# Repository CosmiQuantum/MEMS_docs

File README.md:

# MEMS_docs
Hello and welcome to MEMS in LOUD.  This repository is intended to serve as a central (and sharable) location with instructions and datasheets for the MEMS system.  Control code for the system is stored in the [MEMS_Ctrl](https://github.com/CosmiQuantum/MEMS_Ctrl) repo.  It is kept separate so that users of the system do not need to download this entire handbook to run things.  

This documentation is broken into four categories: 
1. ``LOUD_Electrical`` contains information about the DC cable chain.
2. ``LOUD_Optical`` contains information about the laser routing and control. 
3. ``LOUD_Hardware`` contains information about the design and assembly of the MEMS and qubit housings
4. ``MEMS_Mirrors`` contains mirror datasheets as well as instructions for running the MEMS Windows software (which serves as an alternative to the usb/serial control software linked above).  

----
## What is MEMS
The MEMS laser system can be used to sweep a laser beam across the surface of a given quantum device.  In LOUD, the system is currently hooked up to a 6-qubit [silicon transmon chip](https://github.com/CosmiQuantum/MEMS_docs/blob/main/LOUD_hardware/silicon_qubit_setup.md) from Robert Mcdermott's group at the University of Wisconsin.  A block diagram of the system is shown here:

*Image credit: Kelly Stifter*

-----
## Helpful Links
**MEMS google drive:** https://drive.google.com/drive/folders/1IxKxNAd-OEq4rYUD9z-39MRGrSPkV5Ok?usp=drive_link

**MEMS QSC confluence:** https://confluence.qscience.org/display/1HTCSA/MEMS+System

**Running slide decks:**
* [Planning hardware/wiring for LOUD (8/2022 - present)](https://docs.google.com/presentation/d/1KGMi7ChWB6aNYRg5WBvVhE06Tzbi3BEKmCEu2dWy-tE/edit#slide=id.g2295b13efb6_0_0)
* [MEMS + qubits tests in LOUD (5/2023 - present](https://docs.google.com/presentation/d/11gDJgIZLsgrVuI4iNvbL_12GYMmGFXiDUxQpM1qBsPI/edit#slide=id.g256b424b535_0_0)

----  
## Onboarding resources:
* [Kelly's description of the MEMS program, pre-installation in LOUD (8/2022)](https://docs.google.com/presentation/d/1EdDBv1uNEWqCI73cme1L7-Cg87s-V7iwivkqoPncXTw/edit#slide=id.p)
* [Folder with presentation slides](https://drive.google.com/drive/folders/1UWY2XsLM5ypoSD7gy8bRqhrUESGADwUB)
* Talks available on youtube:
  * *Note that these are both horribly out of date, and do not include results of cold testing. Nevertheless, they may be helpful for students trying to familiarize themselves with the MEMS system & its big-picture goals*
  * [Kelly Stifter, Snowmass 2022](https://www.youtube.com/watch?v=Wy0oarMECdM) (awarded best poster!)
  * [Kelly Stifter, QSC summer school 2022](https://youtu.be/VW6oRTCWZw8?t=2815)

----
## Contact
Please reach out if you have questions or comments.  Even if I'm not around, I'm more than happy to help clarify or troubleshoot.  My contact info is listed here:

| Name | Email | Phone? |
| --- | --- | --- |
| Hannah Magoon | hwmagoon@stanford.edu | 508-665-8282 | 

*I don't want to volunteer the contact info of others, but if you are reading this and have a baseline understanding of the system, please add your name to the table & edit this documentation as you see fit.*

----
## Archived MEMS Links

**MEMS at FNAL photo album:** 
* https://photos.google.com/share/AF1QipMmqoWbn3RVLo4tqv78I0vS4r6iMvlEblVydgLS6NxNUOYILnwoK53Qj7WT-ZwPpg?key=R2o0NlpHQnVBcFBGemhvR2Q4Rk5NVkxOU0pIbUpB
* contains pictures from Lab A and first installation in LOUD (i.e. all MEMS photos from the year 2022)

**MEMS on the NEXUS confluence:** 
* https://confluence.slac.stanford.edu/display/NEXUS/MEMS+mirror+project
* Contains information about the Lab A setup, and project notes pre-Kelly/Hannah
* (Note that more recent documentation can be found on the [QSC confluence](https://confluence.qscience.org/display/1HTCSA/MEMS+System))
  
**Running Slide Decks**
* [MEMS Project Status (1/2023 - present)](https://docs.google.com/presentation/d/1zzwaTrPCd6iAJnR8lv24U-RBMRbJIyfRHySXNWpxKuQ/edit)
* [First cold test in Lab A with Adam's KID (3/2022 - 9/2022)](https://docs.google.com/presentation/d/1kEx_I9y4r-qSOtKWM2qjZcWUeaD-5IixSUfKqjTUWgM/edit#slide=id.g15028d90891_0_0)
* [Lab A datataking (9/2022 - 12/2022)](https://docs.google.com/presentation/d/1aT7D16LCWrzIWNsnplRhRge39xQKbSNosBU8oI7OwhY/edit#slide=id.g1c52c33cf82_0_0)
* [Initial CAD design (3/2022)](https://docs.google.com/presentation/d/1Ot2j-huilQjQEyUlkndx-m_U-fPALiF_-bEYakDAZJo/edit#slide=id.g11e369db084_0_0)
* [Reflective focusing at SLAC (11/2022)](https://docs.google.com/presentation/d/1IvIgyGEyYdLRP5Z9ZWvfET_vtNke7xzl7hGHc7-LfRQ/edit#slide=id.p)
----

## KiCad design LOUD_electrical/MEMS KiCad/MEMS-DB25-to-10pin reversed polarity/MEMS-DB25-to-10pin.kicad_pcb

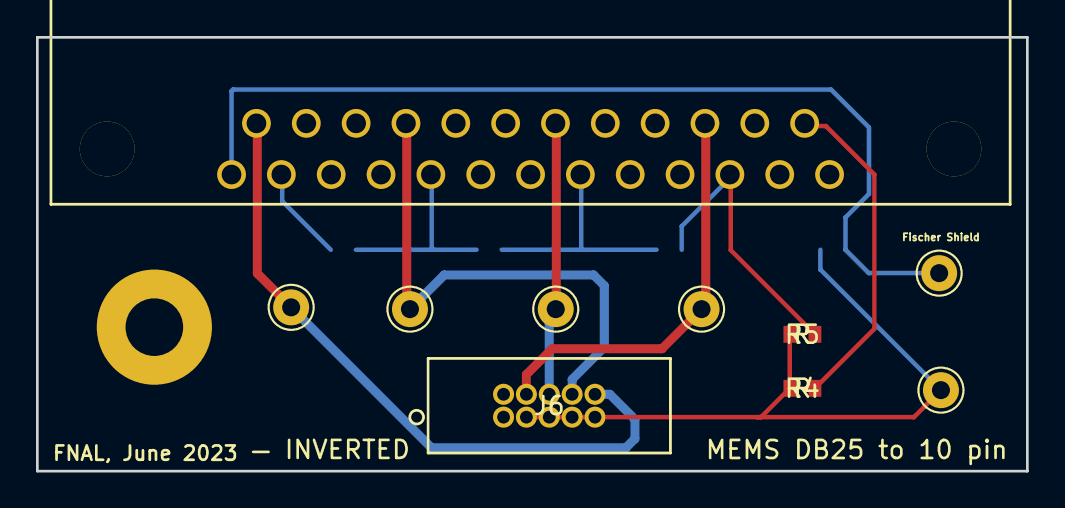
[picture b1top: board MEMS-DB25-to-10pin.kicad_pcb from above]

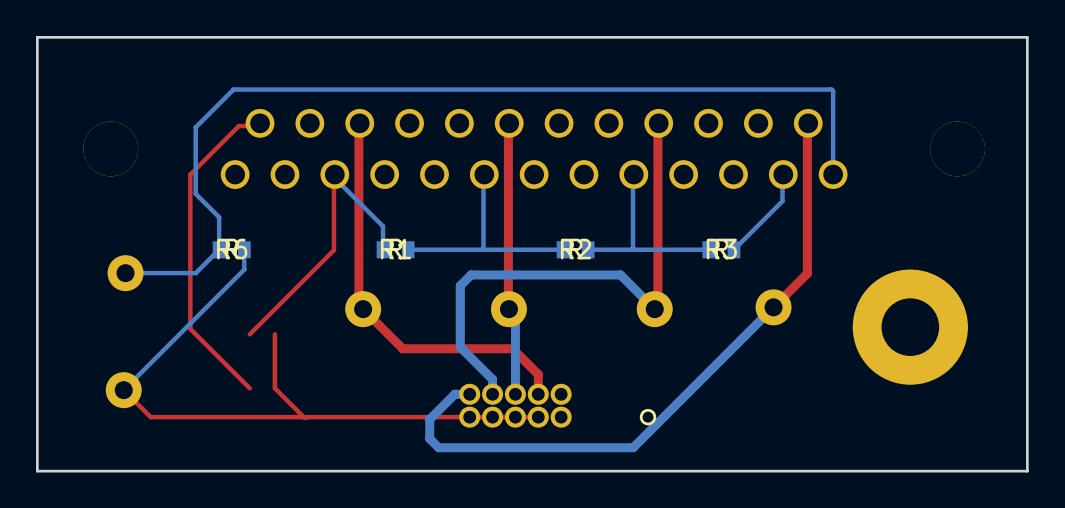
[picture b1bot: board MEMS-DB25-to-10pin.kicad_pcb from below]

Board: 2 copper layers, 55.0 x 24.1 mm, 15 parts (4 on the bottom side), 11 nets.

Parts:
H1: MountingHole; MountingHole_3.2mm_M3_Pad
J1: DB25_Female_MountingHoles; digikey_DSub_NOR1137-ND
J2: X+; Pin_D1.0mm_L10.0mm
J3: X-; Pin_D1.0mm_L10.0mm
J4: Y-; Pin_D1.0mm_L10.0mm
J5: Y+; Pin_D1.0mm_L10.0mm
J6: 3220-10-0100-00; digikey_10pin_1175-1627-ND
J7: GND; Pin_D1.0mm_L10.0mm
J8: Fischer Shield; Pin_D1.0mm_L10.0mm
R1, R2, R3, R4, R5, R6: R; digikey_resistor_RMCF0603ZT0R00

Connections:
unnamed: J1.1, J8.1, R6.1
unnamed: J1.2, R3.2
unnamed: J1.5, R2.2, R3.1
unnamed: J1.8, R1.1, R2.1
unnamed: J1.11, R1.2, R5.2
unnamed: J1.14, J2.1, J6.10
unnamed: J1.17, J3.1, J6.8
unnamed: J1.20, J4.1, J6.6
unnamed: J1.23, J5.1, J6.4
unnamed: J1.25, R4.2
unnamed: J6.3, J6.5, J6.7, J6.9, J7.1, R4.1, R5.1, R6.2

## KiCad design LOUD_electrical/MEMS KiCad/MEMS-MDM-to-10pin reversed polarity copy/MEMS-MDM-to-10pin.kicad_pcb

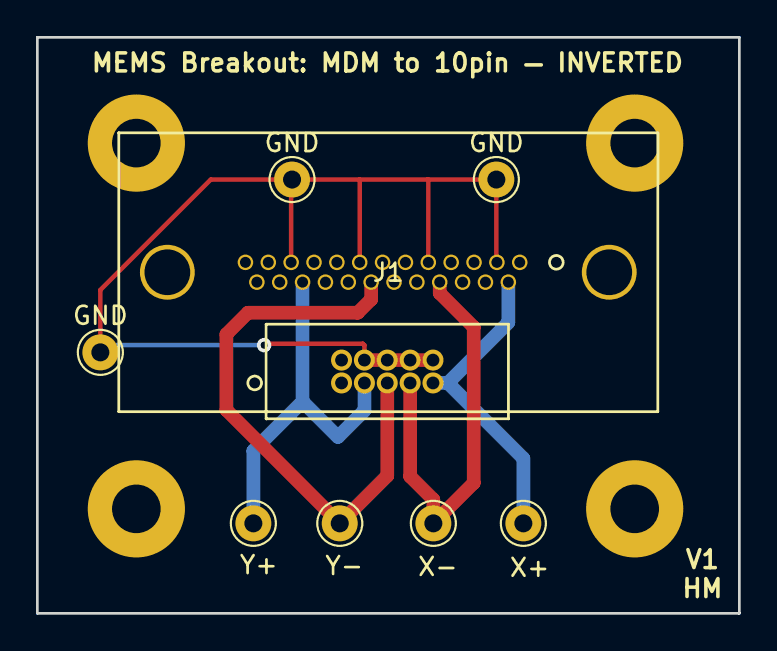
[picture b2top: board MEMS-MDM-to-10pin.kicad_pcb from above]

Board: 2 copper layers, 39.0 x 32.0 mm, 13 parts (0 on the bottom side), 5 nets.

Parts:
H1, H2, H3, H4: MountingHole; MountingHole_2.7mm_M2.5_Pad
J1: DB25_Female_MountingHoles; digikey_MDM_182-25FE-ND
J2: X+; Pin_D1.0mm_L10.0mm
J3, J4, J11: GND; Pin_D1.0mm_L10.0mm
J5: 3220-10-0100-00; digikey_10pin_1175-1627-ND
J6: X-; Pin_D1.0mm_L10.0mm
J7: Y-; Pin_D1.0mm_L10.0mm
J9: Y+; Pin_D1.0mm_L10.0mm

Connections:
unnamed: J1.2, J1.5, J1.8, J1.11, J3.1, J4.1, J5.4, J5.6, J5.8, J5.10, J11.1
unnamed: J1.14, J2.1, J5.9
unnamed: J1.17, J5.7, J6.1
unnamed: J1.20, J5.5, J7.1
unnamed: J1.23, J5.3, J9.1

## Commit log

2023-08-04 pushing little at a time
2023-08-04 mirrors
2023-08-04 docs from my laptop
2023-08-04 make self-consistent
2023-08-04 underscore
2023-08-04 formatting
2023-08-04 adding image
2023-08-04 phrasing
2023-08-04 add images!
2023-08-06 parts list
2023-08-06 pictures
2023-08-07 laser driver readme
2023-08-07 format equations
2023-08-07 format equation
2023-08-07 fix table formatting
2023-08-07 formatting again :/
2023-08-07 make image smaller
2023-08-07 editing instructions
2023-08-07 files from my laptop
2023-08-09 clarify section on thorlabs driver operation modes
2023-08-09 creating mirror FAQ doc
2023-08-09 wrote things
2023-08-09 fix link
2023-08-10 fix filestructure
2023-08-10 brain vomit of a readme
2023-08-10 add text
2023-08-11 clarify phrasing
2023-08-11 finish writing mirror readme
2023-08-11 finish writing Homemade_fischer.md
2023-08-11 update image
2023-08-11 reword
2023-08-11 update to answer noshin's question about hardware_filter
2023-08-11 link to MEMS_mirrors.md for info about datasheets
2023-08-13 outline, for the sake of one commit per day
2023-08-13 outline
2023-08-14 starting edits
2023-09-06 draft procedure
2023-09-06 edits
2023-09-06 screws
2023-09-06 finish writing section
2023-09-10 write text
2023-09-10 ugh typo
2023-09-11 post cable pinouts
2023-09-11 typo
2023-09-11 add thorlabs filter
2023-09-11 edite
2023-09-11 ryan it looks like you might be getting email notifications and if you are im very sorry im multitasking and using this to save edits.
2023-09-11 calculation
2023-09-11 reorder for clarity
2023-09-12 finish editing
2023-09-14 oops fix image placement
2023-09-21 make better
2023-09-21 edit wording
2023-09-21 get rid of empty bullet
2023-09-21 ahh more pictures??
2023-09-21 copy paste error
2023-09-21 yay.
2023-09-21 fix wording again
2024-06-05 fit to a gaussian
2024-06-18 predict optical attenuation down a given fiber path

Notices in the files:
parts and their libraries:
Copyright 2016 Accelerated Designs. All rights reserved.
